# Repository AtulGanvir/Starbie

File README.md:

# ⭐ Starbie — An ESP32-C3 Electronic Pet

Starbie is a DIY electronic pet project built around the **Seeed Studio XIAO ESP32-C3**. It combines embedded systems, sensors, an OLED display, and interactive buttons to create a small electronic companion.

This repository contains my PCB design work as part of **Hack Club Half Life — Week 1: Design Your PCB**.

## 🖼️ PCB 3D Render

*3D visualization of the Starbie PCB design.*

## 🚀 Project Features

- ESP32-C3 microcontroller for embedded control
- OLED display interface using I²C
- MPU6050 motion sensor interface
- DHT11 temperature and humidity sensor
- Two push buttons for user interaction
- Custom PCB layout designed in KiCad

## 🧰 Hardware Components

| Component | Purpose |
|---|---|
| Seeed Studio XIAO ESP32-C3 | Main microcontroller |
| OLED display | Visual output |
| MPU6050 | Motion and orientation sensing |
| DHT11 | Temperature and humidity sensing |
| Push buttons × 2 | User input |
| 10 kΩ resistor | DHT11 data-line pull-up, as configured in the schematic |
| Custom PCB | Connects all components |

## 🔌 Pin Connections

| Component | Signal | XIAO ESP32-C3 connection |
|---|---|---|
| Push button SW1 | GPIO2 | D2 |
| Push button SW2 | GPIO3 | D3 |
| DHT11 | Data | D1 |
| OLED | SCL | D4 |
| OLED | SDA | D5 |
| MPU6050 | SCL | D4 |
| MPU6050 | SDA | D5 |
| OLED / MPU6050 | Power | 3.3V and GND |

*Verify these connections against the final schematic before assembling the hardware.*

## 🛠️ Tools and Technologies

- **KiCad** — Schematic capture and PCB layout
- **ESP32-C3** — Embedded development
- **I²C** — Communication with the OLED and MPU6050
- **PCB Design** — Footprints, routing, and design-rule checking

## 📂 Repository Contents

```text
Starbie/
├── README.md
├── starbie-pcb-render.png
├── myfirstkicad.kicad_pro
├── myfirstkicad.kicad_sch
└── myfirstkicad.kicad_pcb
```

*The KiCad filenames above are examples. Replace them with your actual project filenames, and upload the corresponding files if you want to share the full design.*

## 📈 Current Progress

- [x] Initial schematic and component selection
- [x] PCB placement and routing work
- [x] PCB 3D visualization
- [ ] Resolve remaining KiCad design-rule-check (DRC) errors
- [ ] Verify the final schematic and PCB
- [ ] Manufacture and assemble the PCB
- [ ] Test the hardware and firmware

## 🎯 Project Goal

To learn practical PCB design, embedded electronics, sensor integration, and microcontroller-based development by building an interactive electronic pet.

## 🙌 Acknowledgements

Inspired by the Starbie starter project by SharKingStudios and developed as part of my Hack Club Half Life learning journey.

- [Starbie Project Repository](https://github.com/SharKingStudios/Starbie)
- [KiCad](https://www.kicad.org/)
- [Hack Club Half Life](https://halflife.hackclub.com/)

---

**Made with curiosity and a passion for electronics.** ⚡

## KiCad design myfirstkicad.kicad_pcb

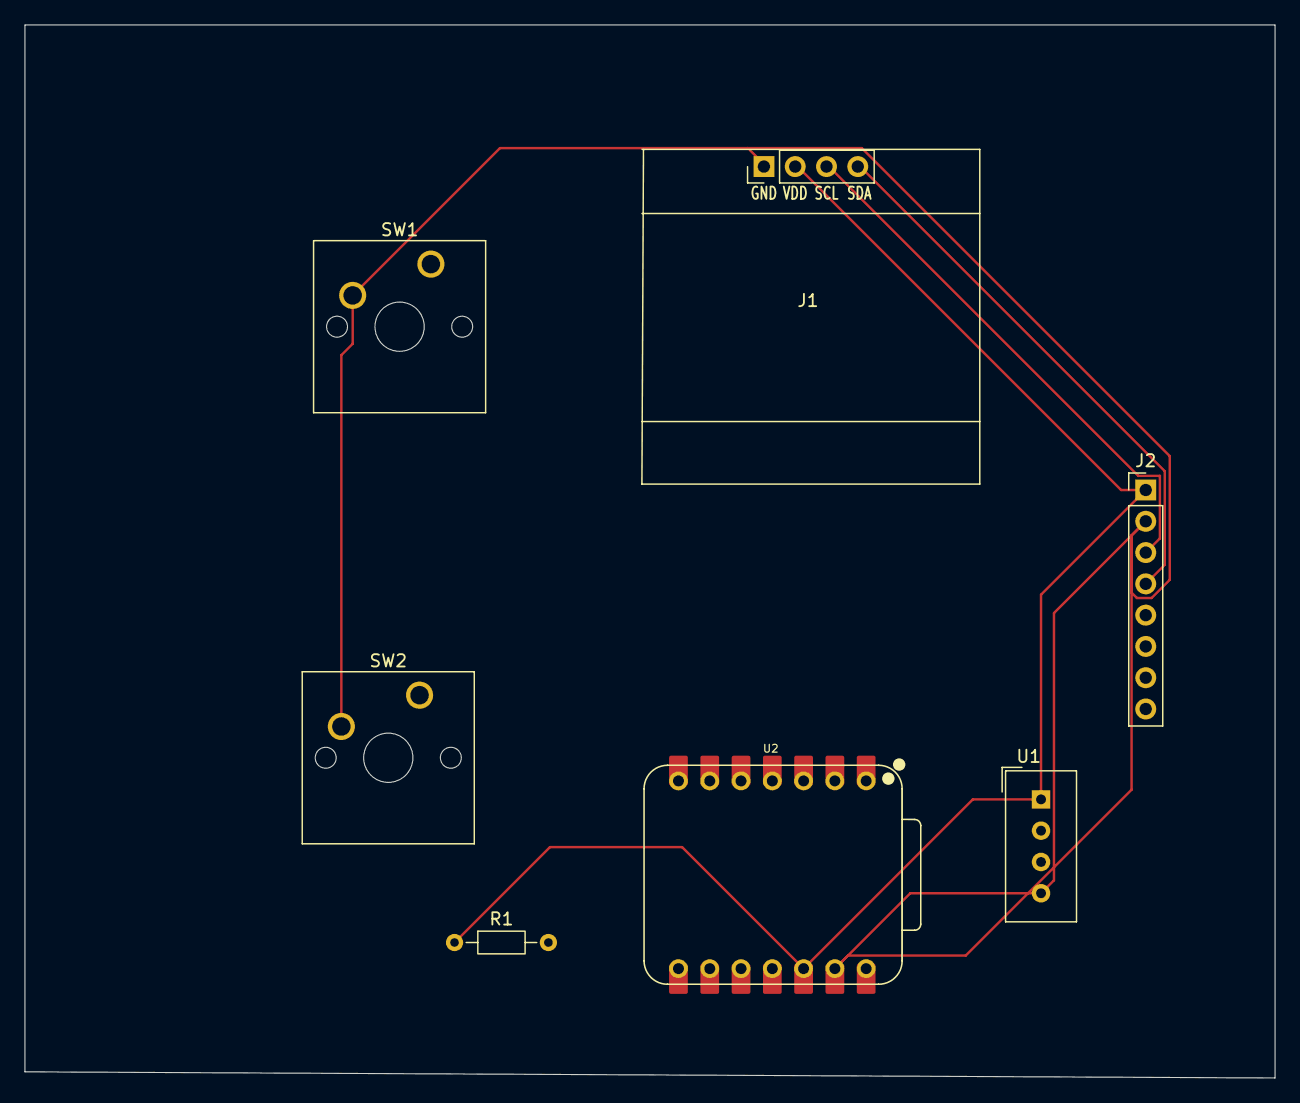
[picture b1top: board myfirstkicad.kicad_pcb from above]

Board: 2 copper layers, 101.5 x 85.5 mm, 7 parts (0 on the bottom side), 4 nets.

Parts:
J1: Conn_01x04_Pin; Display_128x64_096_I2C
J2: Conn_01x08_Pin; PinHeader_1x08_P2.54mm_Vertical
R1: 10k; R_Axial_DIN0204_L3.6mm_D1.6mm_P7.62mm_Horizontal
SW1, SW2: SW_Push; SW_Cherry_MX_1.00u_PCB
U1: DHT11; Aosong_DHT11_5.5x12.0_P2.54mm
U2: XIAO-ESP32-C3-SMD; XIAO-ESP32-C6-DIP

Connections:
+3.3V: J1.2, J2.1, R1.1, U1.1 (VDD), U2.12 (3V3_OUT)
/SCL: J1.3, J2.3
/SDA: J1.4, J2.4
GND: J1.1, J2.2, SW1.2 (2_2), SW2.2 (2_2), U1.4 (GND), U2.13 (GND)
